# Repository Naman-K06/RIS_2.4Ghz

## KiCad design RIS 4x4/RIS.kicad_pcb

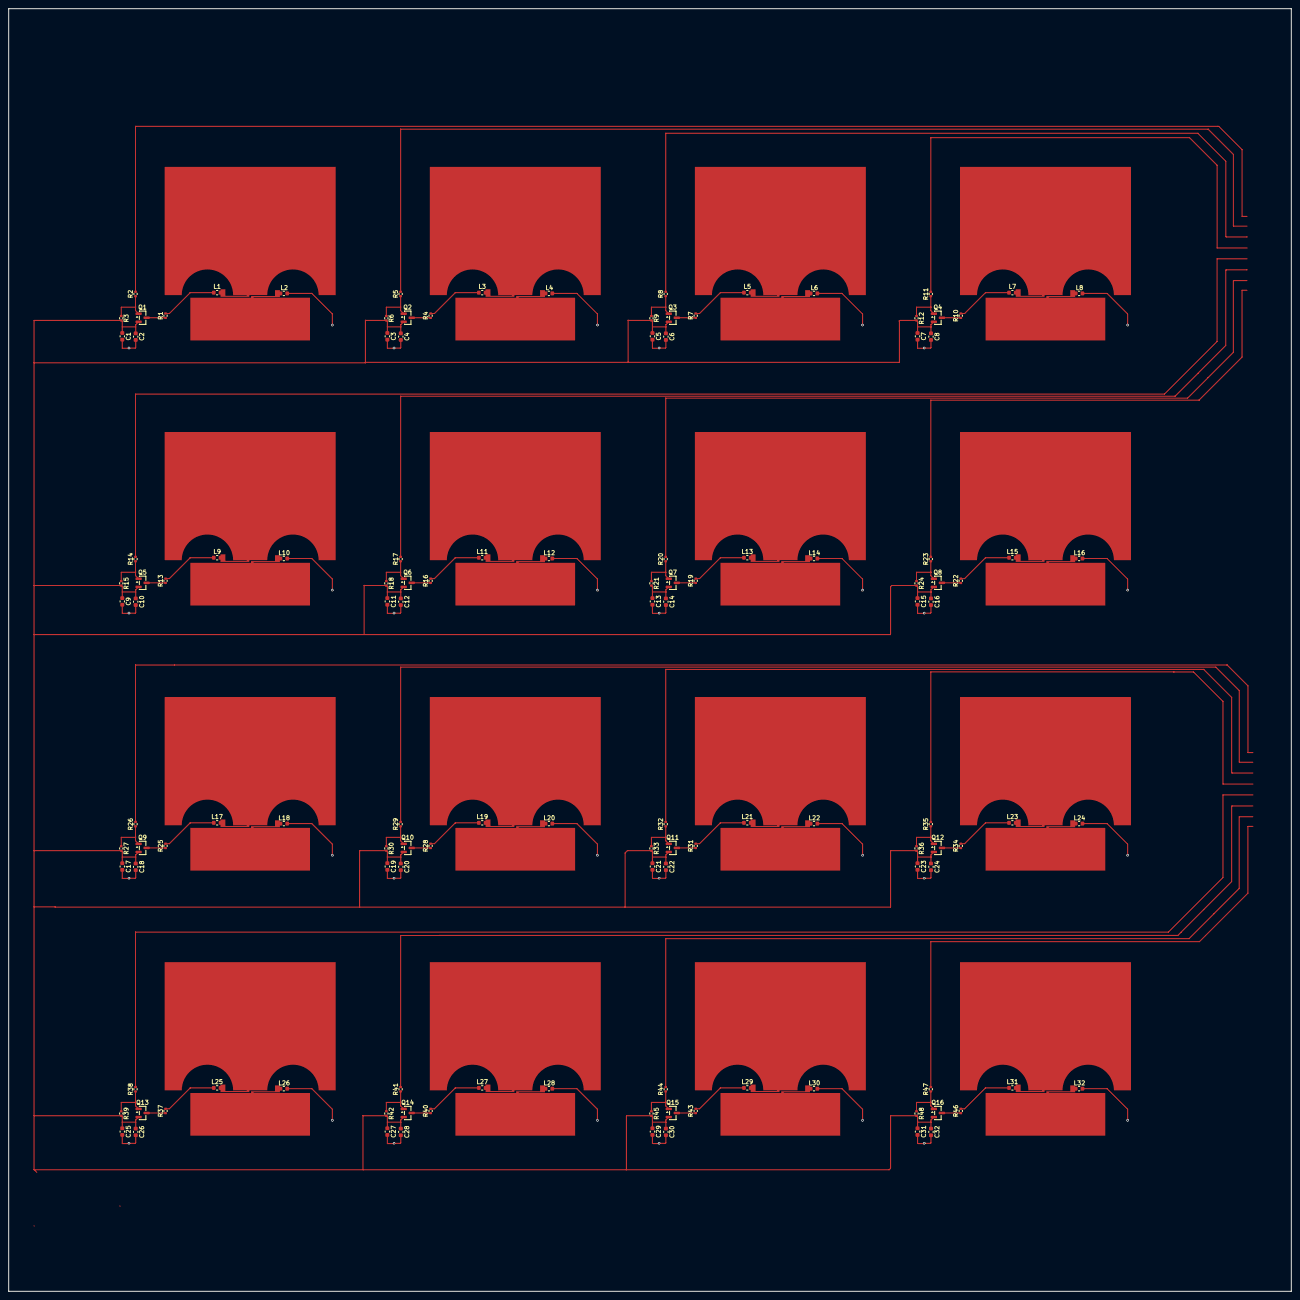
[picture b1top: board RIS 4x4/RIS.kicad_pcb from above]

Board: 2 copper layers, 300.0 x 300.0 mm, 128 parts (0 on the bottom side), 6 nets.

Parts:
C1, C3, C5, C7, C9, C11, C13, C15, C17, C19, C21, C23, C25, C27, C29, C31: 100nF; C_0603_1608Metric
C2, C4, C6, C8, C10, C12, C14, C16, C18, C20, C22, C24, C26, C28, C30, C32: 1uF; C_0603_1608Metric
L1, L2, L3, L4, L5, L6, L7, L8, L9, L10, L11, L12, L13, L14, L15, L16, L17, L18, L19, L20, L21, L22, L23, L24, L25, L26, L27, L28, L29, L30, L31, L32: 22nH; L_0603_1608Metric
Q1, Q2, Q3, Q4, Q5, Q6, Q7, Q8, Q9, Q10, Q11, Q12, Q13, Q14, Q15, Q16: AO3401A; SOT-23
R1, R4, R7, R10, R13, R16, R19, R22, R25, R28, R31, R34, R37, R40, R43, R46: 220 Ω; R_0402_1005Metric
R2, R5, R8, R11, R14, R17, R20, R23, R26, R29, R32, R35, R38, R41, R44, R47: 100 Ω; R_0402_1005Metric
R3, R6, R9, R12, R15, R18, R21, R24, R27, R30, R33, R36, R39, R42, R45, R48: 100 kΩ; R_0402_1005Metric

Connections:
+3.3V: C1.1, C2.1, C3.1, C4.1, C5.1, C6.1, C7.1, C8.1, C9.1, C10.1, C11.1, C12.1, C13.1, C14.1, C15.1, C16.1, C17.1, C18.1, C19.1, C20.1, C21.1, C22.1, C23.1, C24.1, C25.1, C26.1, C27.1, C28.1, C29.1, C30.1, C31.1, C32.1, Q1.2 (S), Q2.2 (S), Q3.2 (S), Q4.2 (S), Q5.2 (S), Q6.2 (S), Q7.2 (S), Q8.2 (S), Q9.2 (S), Q10.2 (S), Q11.2 (S), Q12.2 (S), Q13.2 (S), Q14.2 (S), Q15.2 (S), Q16.2 (S), R3.2, R6.2, R9.2, R12.2, R15.2, R18.2, R21.2, R24.2, R27.2, R30.2, R33.2, R36.2, R39.2, R42.2, R45.2, R48.2
/GPIO: R2.2, R5.2, R8.2, R11.2, R14.2, R17.2, R20.2, R23.2, R26.2, R29.2, R32.2, R35.2, R38.2, R41.2, R44.2, R47.2
GND: C1.2, C2.2, C3.2, C4.2, C5.2, C6.2, C7.2, C8.2, C9.2, C10.2, C11.2, C12.2, C13.2, C14.2, C15.2, C16.2, C17.2, C18.2, C19.2, C20.2, C21.2, C22.2, C23.2, C24.2, C25.2, C26.2, C27.2, C28.2, C29.2, C30.2, C31.2, C32.2, L2.2 (2_2), L4.2 (2_2), L6.2 (2_2), L8.2 (2_2), L10.2 (2_2), L12.2 (2_2), L14.2 (2_2), L16.2 (2_2), L18.2 (2_2), L20.2 (2_2), L22.2 (2_2), L24.2 (2_2), L26.2 (2_2), L28.2 (2_2), L30.2 (2_2), L32.2 (2_2)
unnamed: L1.1 (1_1), L3.1 (1_1), L5.1 (1_1), L7.1 (1_1), L9.1 (1_1), L11.1 (1_1), L13.1 (1_1), L15.1 (1_1), L17.1 (1_1), L19.1 (1_1), L21.1 (1_1), L23.1 (1_1), L25.1 (1_1), L27.1 (1_1), L29.1 (1_1), L31.1 (1_1), R1.2, R4.2, R7.2, R10.2, R13.2, R16.2, R19.2, R22.2, R25.2, R28.2, R31.2, R34.2, R37.2, R40.2, R43.2, R46.2
unnamed: Q1.3 (D), Q2.3 (D), Q3.3 (D), Q4.3 (D), Q5.3 (D), Q6.3 (D), Q7.3 (D), Q8.3 (D), Q9.3 (D), Q10.3 (D), Q11.3 (D), Q12.3 (D), Q13.3 (D), Q14.3 (D), Q15.3 (D), Q16.3 (D), R1.1, R4.1, R7.1, R10.1, R13.1, R16.1, R19.1, R22.1, R25.1, R28.1, R31.1, R34.1, R37.1, R40.1, R43.1, R46.1
unnamed: Q1.1 (G), Q2.1 (G), Q3.1 (G), Q4.1 (G), Q5.1 (G), Q6.1 (G), Q7.1 (G), Q8.1 (G), Q9.1 (G), Q10.1 (G), Q11.1 (G), Q12.1 (G), Q13.1 (G), Q14.1 (G), Q15.1 (G), Q16.1 (G), R2.1, R3.1, R5.1, R6.1, R8.1, R9.1, R11.1, R12.1, R14.1, R15.1, R17.1, R18.1, R20.1, R21.1, R23.1, R24.1, R26.1, R27.1, R29.1, R30.1, R32.1, R33.1, R35.1, R36.1, R38.1, R39.1, R41.1, R42.1, R44.1, R45.1, R47.1, R48.1

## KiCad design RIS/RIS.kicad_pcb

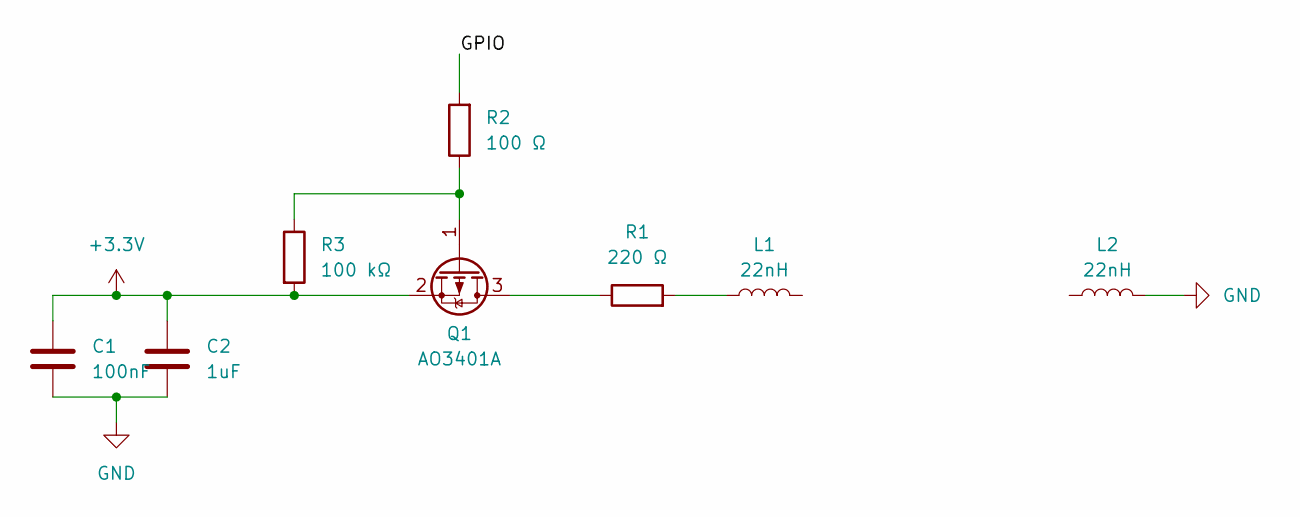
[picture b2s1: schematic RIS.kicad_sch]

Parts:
C1: 100nF; C_0603_1608Metric
C2: 1uF; C_0603_1608Metric
L1, L2: 22nH; L_0603_1608Metric
Q1: AO3401A; SOT-23
R1: 220 Ω; R_0402_1005Metric
R2: 100 Ω; R_0402_1005Metric
R3: 100 kΩ; R_0402_1005Metric

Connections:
+3.3V: C1.1, C2.1, Q1.2 (S), R3.2
/GPIO: R2.2
GND: C1.2, C2.2, L2.2 (2_2)
unnamed: L1.1 (1_1), R1.2
unnamed: Q1.3 (D), R1.1
unnamed: Q1.1 (G), R2.1, R3.1

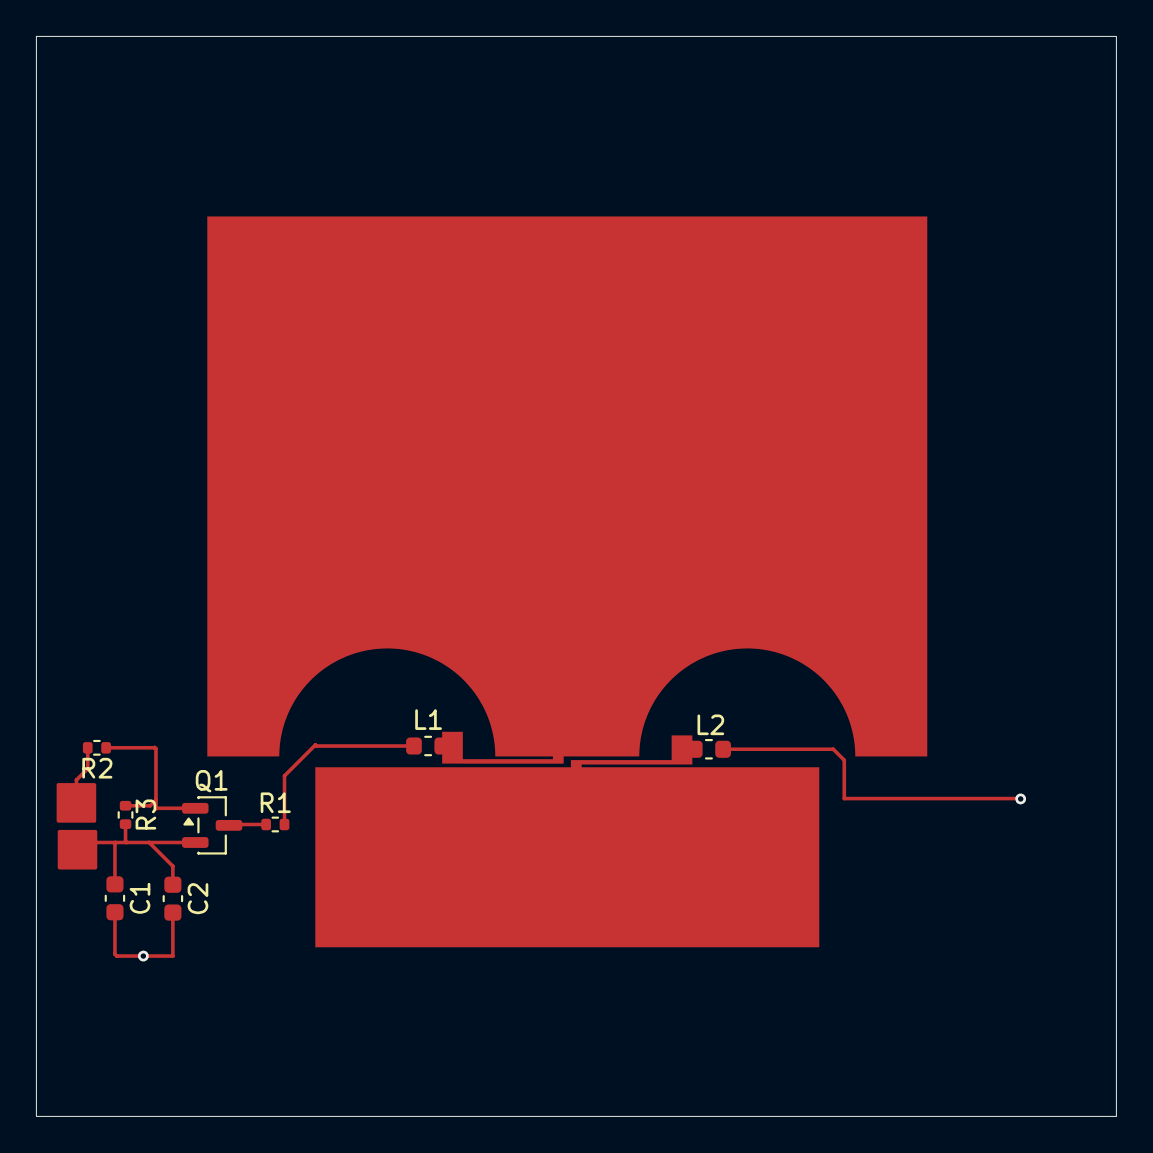
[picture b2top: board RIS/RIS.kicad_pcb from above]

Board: 2 copper layers, 60.0 x 60.0 mm, 8 parts (0 on the bottom side), 5 nets.
